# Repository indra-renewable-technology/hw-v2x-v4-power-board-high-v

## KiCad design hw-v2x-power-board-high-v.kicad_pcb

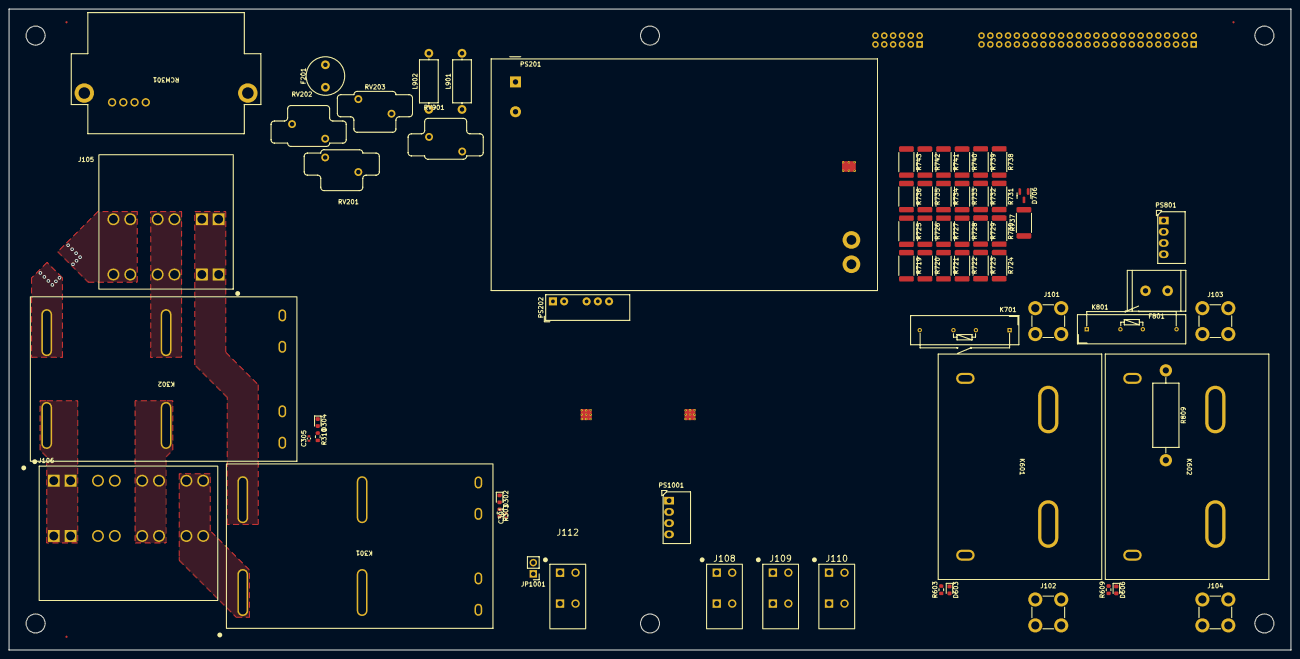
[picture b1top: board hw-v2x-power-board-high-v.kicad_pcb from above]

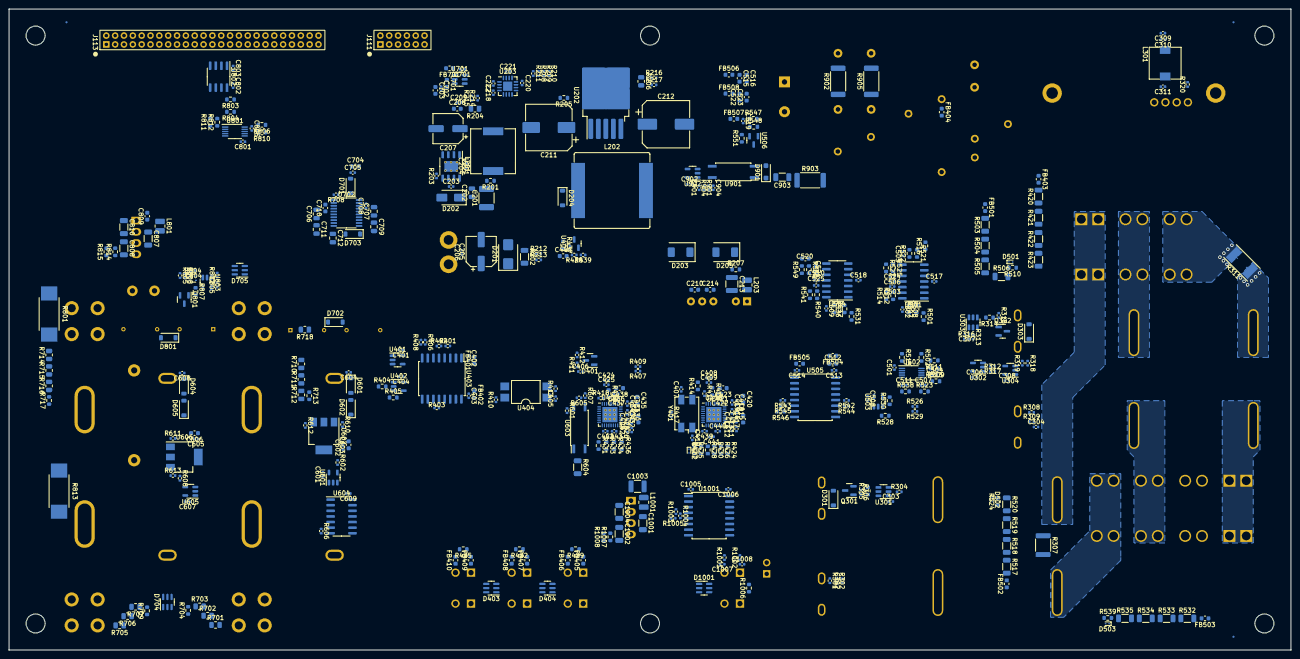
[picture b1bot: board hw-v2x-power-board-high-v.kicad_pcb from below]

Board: 2 copper layers, 290.0 x 145.0 mm, 492 parts (416 on the bottom side), 281 nets.

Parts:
C201: 100uF; C_1812_4532Metric
C202: 10uF; C_0805_2012Metric
C203, C206, C209, C218, C220, C221, C222, C301, C302, C303, C304, C305, C306, C307, C308, C310, C311, C401, C402, C403, C404, C405, C406, C411, C413, C415, C418, C421, C426, C428, C430, C433, C436, C501, C508, C513, C514, C517, C518, C519, C524, C525, C601, C602, C604, C605, C607, C608, C609, C701, C702, C705, C708, C801, C802, C803, C804, C805, C806, C902, C1005, C1006: 0.1uF; C_0402_1005Metric
C204, C408, C424, C440, C441, C442, C443: 10nF; C_0402_1005Metric
C205: 47uF; CP_Elec_6.3x7.7
C207: 100uF; CP_Elec_6.3x7.7
C208, C210, C214, C417, C420, C423, C432, C435, C438, C516, C521, C523, C603, C606: 1uF; C_0603_1608Metric
C211: 100uF; CP_Elec_10x10
C212: 470uF; CP_Elec_10x10.5
C213: 2.2uF; C_1210_3225Metric
C309, C901: 1uF; C_0402_1005Metric
C407, C410: 15pF; C_0402_1005Metric
C409, C412, C414, C416, C419, C422, C425, C427, C429, C431, C434, C437, C504, C507, C511: 150pF; C_0402_1005Metric
C439: 22nF; C_0402_1005Metric
C444, C512, C515, C520, C522: 4.7uF; C_0603_1608Metric
C502, C503, C505, C506, C509, C510: 82nF; C_0402_1005Metric
C703, C704, C809: 10uF; C_0603_1608Metric
C706, C707, C709, C711, C712: 22uF; C_0805_2012Metric
C710: 680nF; C_0603_1608Metric
C807, C810, C1001, C1004: 330pF; C_1206_3216Metric
C808, C1002: 47uF; C_1206_3216Metric
C903: 2n2 1kV; C_1206_3216Metric
C904: 220nF; C_0402_1005Metric
C1003: 10uF; C_1210_3225Metric
C1007, C1008: 47pF; C_0402_1005Metric
D201: P6SMB16A; D_SMB
D202: B320AQ-13-F; D_SMA
D203, D205: SMLVT3V3; SMLVT_SMB
D204: 1N5822; D_SOD-123
D301, D303, D601, D604, D702, D801: B130LAW-7-F; D_SOD-123
D302, D304, D603, D606: Green LED; LED_0603_1608Metric
D401: BAT54C; SOT-23
D402, D501, D502, D503: ESD9B3.3ST5G; D_SOD-923
D403, D404, D704, D705, D1001: CM1293A-04SO; SC-74-6_1.5x2.9mm_P0.95mm
D602, D605: BZT52C36-7-F; D_SOD-123
D701, D703: BAT43W; D_SOD-123
D706: BAV99; SOT-23
D901: SM4007PL-TP; D_SOD-123F
F201: 500mA; 37205000001
F801: TRF600-150-RB; R_Radial_Power_L13.0mm_W9.0mm_P5.00mm
FB401, FB402, FB403, FB404, FB405, FB406, FB407, FB408, FB409, FB410, FB501, FB502, FB503, FB504, FB505, FB506, FB507, FB508, FB701: BLM18AG102SN1D; L_0603_1608Metric
FID101, FID102, FID103, FID104, FID105, FID106: Fiducial; Fiducial_0.5mm_Mask1mm
H101, H102, H103, H104, H105, H106: MountingHole; MountingHole_4.3mm_M4
J101, J102, J103, J104: 74651175R; Wuerth_REDCUBE-THR_WP-THRSH_74651175_THR
J105: NZ 03000B0000G; AMPHENOL_NZ_0300xBxxxxG_3_PIN_CONNECTOR
J106: NZ 04000B0000G; AMPHENOL_NZ_0400xBxxxxG_4_PIN_CONNECTOR
J108, J109, J110, J112: TBLH10-350-02BK; CUI_TBLH10-350-02BK_2_PIN_CONNECTOR
J111: M22-7140642; HARWIN_M22-7140642_12_PIN_CONNECTOR
J113: M22-7142542; HARWIN_M22-7142542_50_PIN_CONNECTOR
JP1001: NO; PinHeader_1x02_P2.54mm_Vertical
K301, K302: AHER2281
K601, K602: OMRON_G9KB-1A; G9KB-1A_DCxx
K701, K801: SHV05-1A85
L201: 15uH; L_Wuerth_WE-TPC_SMT_Shielded
L202: 100uH; L_Bourns_SRP1770TA_16.9x16.9mm
L203, L801, L1001: 22uH; L_1008_2520Metric
L301: 220uH; L_Bourns-SRR7045
L701: 10uH; L_0603_1608Metric
L901, L902: 47uH; L_Axial_L9.5mm_D4.0mm_P12.70mm_Horizontal_Fastron_SMCC
PS201: IRM-60-12; Converter_ACDC_MeanWell_IRM-60-xx_THT
PS202: IA0503S; Converter_DCDC_XP_POWER-IAxxxxS_THT
PS801, PS1001: ROE-1205S
Q301, Q302: DMG2302UK-7; SOT-23
Q801: MMBT5550LT1G; SOT-23
R201, R205, R207, R404, R405, R414, R427, R528, R530, R546, R811, R812: 0R; R_0603_1608Metric
R202: 0.01R; R_1206_3216Metric
R203: 470K; R_0402_1005Metric
R204, R206: 0.033R; R_0805_2012Metric
R208, R209, R210, R211, R301, R302, R306, R308, R309, R315, R320, R406, R407, R408, R409, R415, R418, R526, R529, R708, R1005: 10K; R_0402_1005Metric
R212, R213, R214, R215, R216, R217: 10R; R_0402_1005Metric
R303, R310, R603, R609: 1.8K; R_0603_1608Metric
R304, R312, R313, R317, R318, R319, R602, R608: 4.7K; R_0402_1005Metric
R305, R314, R437, R509, R523, R538: 15R; R_0603_1608Metric
R307: 0R; R_1812_4532Metric
R311: 0.5mR; WSLF2512L5000F
R316, R606, R607, R612, R613, R802, R805: 100K; R_0402_1005Metric
R401, R402, R403, R410, R412: 10k; R_0402_1005Metric
R411, R901: 100R; R_0402_1005Metric
R413, R808: 470R; R_0402_1005Metric
R416, R419, R502, R511, R513, R515: 100R; R_0603_1608Metric
R417: 1M; R_0402_1005Metric
R420, R421, R422, R423, R503, R504, R505, R506, R517, R518, R519, R520, R532, R533, R534, R535: 100K; R_1206_3216Metric
R424, R426, R428, R430, R431, R433, R434, R436, R510: 1K; R_0603_1608Metric
R425: 232R; R_0603_1608Metric
R429, R432, R435: 6.04R; R_0603_1608Metric
R438: 750R; R_0402_1005Metric
R439: 3.16K; R_0402_1005Metric
R501, R507, R508, R512, R514, R516, R521, R522, R525, R527, R531, R536, R537, R540, R541: 10K; R_0603_1608Metric
R524, R539: 2.2K; R_0603_1608Metric
R542, R543, R544, R545, R601, R605: 1K; R_0402_1005Metric
R547: 210R; R_0603_1608Metric
R548: 316R; R_0603_1608Metric
R549, R550, R807: 4.7K; R_0603_1608Metric
R551: 3.16K; R_0603_1608Metric
R604: 620R; R_1206_3216Metric
R610, R611: 47K; R_0402_1005Metric
R701, R702, R703, R705, R706, R707, R710, R711, R712, R714, R715, R716: 240K; R_0805_2012Metric
R704, R709, R713, R717: 3.6K; R_0603_1608Metric
R718: 0R; R_0805_2012Metric
R719, R720, R721, R722, R723, R724, R725, R726, R727, R728, R729, R730, R731, R732, R733, R734, R735, R736, R738, R739, R740, R741, R742, R743: 120K; R_2512_6332Metric
R737: 200R; R_2512_6332Metric
R801, R813: 10R; R_BOURNS_PWR4318
R803, R804: 3K; R_0603_1608Metric
R806, R810: 10R; R_0603_1608Metric
R809: 1R; R_Axial_DIN0614_L14.3mm_D5.7mm_P20.32mm_Horizontal
R814, R815, R1007, R1008: 470R; R_0603_1608Metric
R902, R905: 220R; R_2512_6332Metric
R903: 820K; R_2512_6332Metric
R904: 39K; R_0402_1005Metric
R1001, R1002, R1003, R1004: 0R; R_0402_1005Metric
R1006: 120R; R_0603_1608Metric
RCM301: RCM-EV-02_P
RV201, RV202, RV203, RV901: B72214R2301K101
U201: LM22670; HSOP-8-1EP_3.9x4.9mm_P1.27mm_EP2.41x3.1mm_ThermalVias
U202: LM2576D2TR4-3.3G; TO-263-5_TabPin3
U203: INA3221; Texas_RGV_S-PVQFN-N16_EP2.1x2.1mm
U301, U303: ZXGD3009E6; SOT-23-6
U302, U304: SN74AHC1G08; SOT-23-5
U401: 74AHC1G08; SOT-23-5
U402: 74AHC1G125_X; SOT-23-5
U403, U505: ISO6761DWR; SOIC-16W_7.5x10.3mm_P1.27mm
U404: LTV-817S; SMDIP-4_W9.53mm
U405: STPM33; QFN-32-1EP_5x5mm_P0.5mm_EP3.45x3.45mm_ThermalVias
U406: STPM34; QFN-32-1EP_5x5mm_P0.5mm_EP3.45x3.45mm_ThermalVias
U407, U506: TL431DBZ; SOT-23
U501, U504: MC33174; SOIC-14_3.9x8.7mm_P1.27mm
U502: ADC124S021; VSSOP-10_3x3mm_P0.5mm
U503: 74AHC1G125; SOT-23-5
U601, U605, U803: 74LVC1G08; SOT-23-5
U602, U606: ITS4200SMENHUMA1; SOT-223
U603, U901: HCPL-817-56AE; SO-4_7.6x3.6mm_P2.54mm
U604: 74LV21; SO-14_3.9x8.65mm_P1.27mm
U701: LM2664; SOT-23-6
U702: AD7327; TSSOP-20_4.4x6.5mm_P0.65mm
U801: INA226; VSSOP-10_3x3mm_P0.5mm
U802: Si8602; SOIC-8_3.9x4.9mm_P1.27mm
U804: NL17SZ14; SOT-553
U902: LM321; SOT-23-5
U1001: ISO3082DW; SOIC-16W_7.5x10.3mm_P1.27mm
Y401: 16MHz; Crystal_SMD_EuroQuartz_MQ-4Pin_7.0x5.0mm

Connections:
0V_iso: C210.2, C214.1, C403.1, C405.1, C406.2, C407.2, C408.1, C409.1, C410.2, C411.1, C412.1, C413.1, C414.1, C415.1, C416.1, C417.1, C418.1, C419.1, C420.1, C421.1, C422.1, C423.1, C424.1, C425.1, C426.1, C427.1, C428.1, C429.1, C430.1, C431.1, C432.1, C433.1, C434.1, C435.1, C436.1, C437.1, C438.1, C444.1, D203.2 (A2), D205.1 (A1), D403.2 (VN), D404.2 (VN), FB406.2, FB408.2, FB410.2, PS202.5 (0V), R409.2, R412.1, R427.1, R429.2, R430.2, R432.2, R433.2, R435.2, R436.2, R439.1, U403.9 (GND2), U405.18 (GND_REF), U405.20 (GNDA), U405.22 (GND_REF), U405.26 (GNDD), U405.33 (PAD), U406.3 (XTAL1), U406.18 (GND_REF), U406.20 (GNDA), U406.22 (GND_REF), U406.26 (GNDD), U406.33 (PAD), U407.3 (A), Y401.2, Y401.4
3V3_iso: C210.1, C508.1, D203.1 (A1), D403.5, D404.5, FB402.1, FB504.2, FB506.1, PS202.6 (+Vout), R407.1, R415.1, R418.1, R437.1, R526.1, U503.5
+3.3V: C218.2, C303.1, C306.1, C307.1, C308.1, C401.1, C404.1, C601.2, C607.2, C609.1, C708.1, C803.1, C804.1, C805.1, C902.1, C1005.1, FB401.1, FB505.2, J111.9, J111.11, R206.1, R208.1, R209.1, R210.1, R211.1, R216.1, R301.2, R308.2, R320.2, R401.2, R402.2, R406.1, R410.1, R601.2, R605.2, R708.1, R805.2, R901.1, U203.4 (VS), U203.5 (A0), U203.16 (VPU), U301.1 (VCC), U302.5 (VCC), U303.1 (VCC), U304.5 (VCC), U401.5 (VCC), U402.5, U601.5 (VCC), U604.1, U604.5, U604.14 (VCC), U605.5 (VCC), U702.17 (VDRIVE), U802.1 (AVDD), U803.5 (VCC), U804.5 (VCC), U902.5 (V+), U1001.1 (Vcc1)
+5V: C309.1, C310.1, C704.1, C705.1, D701.2 (A), D702.1 (K), D704.5, D705.5, D706.2 (A), D801.1 (K), J111.5, J111.7, K701.2, K801.2, L301.1, R204.1, R207.2, R214.1, U701.4 (~SD), U701.5 (V+), U702.16 (VCC)
+5V_ISO1: C1001.2, C1002.2, C1006.1, D1001.5, PS1001.4 (+Vout), R1007.1, R1008.1, U1001.16 (Vcc2)
+12V: C301.1, C602.1, C603.1, C605.1, C606.1, C809.2, C1003.2, D301.1 (K), J111.1, J111.3, K301.3, K301.5, L801.1, L1001.1, R201.1, R202.1, R205.2, R212.1, R303.2, U602.4 (IN), U606.4 (IN)
-3V3_iso: C214.2, D205.2 (A2), FB508.1, PS202.4 (-Vout)
/1P_SHUNT_L1_N: R311.2, R426.2
/1P_SHUNT_L1_P: R311.3, R424.2
/A7NS_I2C1_SCL: J113.24, U203.6 (SCL), U802.3 (ASCL)
/A7NS_I2C1_SDA: J113.28, U203.7 (SDA), U802.2 (ASDA)
/A7NS_SPI1_CLK: J113.35, U403.2 (INA), U702.20 (SCLK)
/A7NS_SPI1_MISO: J113.39, R405.2, U402.4, U702.18 (DOUT)
/A7NS_SPI1_MOSI: J113.43, U403.3 (INB), U702.2 (DIN)
/AC-metering/clk_stpm: R414.1, U405.1 (CLKOUT), U406.2 (XTAL2)
/AC-metering/cs1: R415.2, U403.13 (OUTC), U405.29 (SCS)
/AC-metering/cs2: R418.2, U403.12 (OUTD), U406.29 (SCS)
/AC-metering/en: C406.1, R411.1, U405.8 (EN), U406.8 (EN)
/AC-metering/iin_L1: C440.1, R426.1, U405.13 (IIN2)
/AC-metering/iin_ext_aux_1: C442.1, R433.1, U406.12 (IIN1)
/AC-metering/iin_ext_aux_2: C443.1, R436.1, U406.14 (IIP2)
/AC-metering/iin_ext_house: C441.1, R430.1, U405.12 (IIN1)
/AC-metering/iip_L1: C440.2, R424.1, U405.14 (IIP2)
/AC-metering/iip_ext_aux_1: C442.2, R431.1, U406.11 (IIP1)
/AC-metering/iip_ext_aux_2: C443.2, R434.1, U406.13 (IIN2)
/AC-metering/iip_ext_house: C441.2, R428.1, U405.11 (IIP1)
/AC-metering/metering_ext_aux_ct_1_neg: D404.6, FB408.1, J109.2
/AC-metering/metering_ext_aux_ct_1_pos: D404.4, FB407.1, J109.1
/AC-metering/metering_ext_aux_ct_2_neg: D403.6, FB410.1, J110.2
/AC-metering/metering_ext_aux_ct_2_pos: D403.4, FB409.1, J110.1
/AC-metering/metering_ext_house_ct_neg: D404.3 (CH1), FB406.1, J108.2
/AC-metering/metering_ext_house_ct_pos: D404.1 (CH1), FB405.1, J108.1
/AC-metering/mi: R404.1, R405.1, R406.2, R408.1, U403.7 (OUTF)
/AC-metering/miso: R407.2, R409.1, U403.10 (INF), U405.32 (MISO), U406.32 (MISO)
/AC-metering/mosi: U403.14 (OUTB), U405.31 (MOSI), U406.31 (MOSI)
/AC-metering/sclk: D401.1, U403.15 (OUTA), U405.30 (SCL), U406.30 (SCL)
/AC-metering/syn: C408.2, C409.2, C424.2, C425.2, D401.2, R403.1, R416.1, R419.1, U403.11 (OUTE)
/AC-metering/v_stpm: C405.2, C418.2, C419.2, C420.2, C433.2, C434.2, C435.2, C444.2, R403.2, R437.2, R438.2, U404.1, U405.23 (VCC), U406.23 (VCC), U407.1 (K)
/AC-metering/vip_L1: C439.2, D402.1 (A1), R423.1, R425.1, U405.9 (VIP1), U406.9 (VIP1), U406.16 (VIP2)
/AC-metering/vip_N1: C439.1, D402.2 (A2), FB404.2, R425.2, R427.2, U405.10 (VIN1), U406.10 (VIN1), U406.15 (VIN2)
/AC-metering/zcr: R413.1, R414.2, U406.1 (CLKOUT)
/AC-switching/12v_switched: C305.1, D303.1 (K), K301.10, K302.5, R310.2
/AC-switching/ac_cpc_out: J105.1, K301.12, R307.1
/AC-switching/ac_l1_out: J105.2, K302.10
/AC-switching/ac_neutral_out: J105.3, R311.4
/AC-switching/neut_sw: K302.12, R311.1
/AC_EARTH_RELAY_EN: J113.32, R304.2
/AC_EARTH_RELAY_SENSE: C302.1, J113.40, R302.2
/AC_POWER_RELAY_EN: J113.34, R312.2
/AC_POWER_RELAY_SENSE: C304.1, J113.38, R309.2
/AC_RCM_TEST: J113.44, RCM301.3 (TEST)
/CPC_IN: FB502.1, J106.4, K301.1, R307.2, RV202.2, RV203.2
/DC-switching-and-measurement/HVDC-insulation-leakage-detection/+5V_ISO: C801.1, C802.2, C807.2, C808.2, PS801.4 (+Vout), R803.1, R804.1, R814.1, R815.1, U801.6 (VS), U802.8 (BVDD)
/DC-switching-and-measurement/HVDC-insulation-leakage-detection/GND_ISO: C801.2, C802.1, C808.1, C810.2, PS801.3 (-Vout), R809.2, R810.1, R811.2, R812.2, R813.1, R814.2, R815.2, U801.7 (GND), U802.5 (BGND)
/DC-switching-and-measurement/HVDC-insulation-leakage-detection/shunt_high: K801.1, R806.1, R809.1, U801.8 (Vbus)
/DC-switching-and-measurement/HVDC-voltage-measurement/-5V: C702.1, C703.1, D703.1 (K), D706.1 (K), L701.2
/DC-switching-and-measurement/HVDC-voltage-measurement/AGND: C704.2, C705.2, C706.2, C707.2, C709.2, C710.2, C711.2, C712.2, D704.2 (VN), D705.2 (VN), FB701.2, R704.1, R709.1, R713.1, R717.1, R737.1, U702.4 (AGND), U702.7 (VIN0), U702.11 (VIN7), U702.12 (VIN6)
/DC-switching-and-measurement/HVDC-voltage-measurement/dc_sense_battery_pos_swi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: K701.4, R710.2, R718.1, R719.2, R720.2, R721.2, R722.2, R723.2, R724.2
/DC-switching-and-measurement/dc_input_battery_neg: J103.1, K602.3, R714.2, R738.1, R739.1, R740.1, R741.1, R742.1, R743.1, R801.2
/DC-switching-and-measurement/dc_input_battery_pos: J101.1, K601.3, K701.1, R718.2
/DC-switching-and-measurement/dc_neg_contactor_drive: C608.1, D604.1 (K), K602.1, R609.2, R611.1, U606.1 (OUT)
/DC-switching-and-measurement/dc_neg_en: R608.2, R805.1, R808.1, U605.4
/DC-switching-and-measurement/dc_output_inverter_neg: J104.1, K602.4, R705.2, R813.2
/DC-switching-and-measurement/dc_output_inverter_pos: J102.1, K601.4, R701.2
/DC-switching-and-measurement/dc_pos_contactor_drive: C604.1, D601.1 (K), K601.1, R603.2, R610.1, U602.1 (OUT)
/DC-switching-and-measurement/dc_pos_en: R602.2, U601.4
/DC_CONTACTOR_NEG: J113.13, U605.1
/DC_CONTACTOR_POS: J113.11, U601.1
/DC_I_SHUNT_EN: J113.19, R802.1, U803.1
/DC_VOLTAGE_CS: J113.5, R708.2, U702.1 (~CS)
/ESTOP_LATCH: J113.17, R318.2, U604.2
/HVIL_MON: J113.7, R605.1, R607.2, U603.3, U604.4
/L1_IN: F201.1, FB403.1, FB501.1, J106.3, K302.3, RV201.1, RV202.1
/M4_SPI2_CLK: J113.14, U505.2 (INA)
/M4_SPI2_MISO: J113.6, R546.2
/M4_SPI2_MOSI: J113.10, U505.3 (INB)
/METERING_CS1: J113.16, R401.1, U401.1, U403.4 (INC)
/METERING_CS2: J113.18, R402.1, U401.2, U403.5 (IND)
/METERING_SYN: J113.27, U403.6 (INE)
/METERING_ZCR: J113.23, R410.2, U404.4
/NEUTRAL_IN: C501.2, C503.2, C504.2, C506.2, C507.2, C508.2, C510.2, C511.2, C512.1, C513.2, C515.2, C516.2, C517.2, C518.2, C519.2, C520.2, C521.2, C522.1, C523.1, C524.1, C525.1, D501.2 (A2), D502.2 (A2), D503.2 (A2), FB404.1, J106.1, K302.1, PS201.2 (AC/N), R510.1, R514.1, R524.1, R527.1, R529.2, R539.1, R541.1, R542.1, R544.1, R550.1, R551.1, RV201.2, RV203.1, U502.3 (GND), U503.3, U504.5 (+), U505.9 (GND2), U506.3 (A)
/PESTS_CS: J113.20, U505.4 (INC)
/PESTSs/buf_miso: R530.2, U503.4, U505.10 (INF)
/PESTSs/cpc_neutral_meas: C507.1, R523.1, U502.6 (IN2)
/PESTSs/l1_neutral_meas: C504.1, R509.1, U502.7 (IN1)
/PESTSs/miso: R511.1, R526.2, R528.1, R529.1, R530.1
/PESTSs/mosi: R513.1, U505.14 (OUTB)
/PESTSs/sclk: R502.1, U505.15 (OUTA)
/PESTSs/tt_ref_neutral_meas: C511.1, R538.1, U502.5 (IN3)
/PESTSs/v_mid_ref: R501.2, R516.2, R531.2, U502.4 (IN4), U504.8, U504.9 (-)
/PESTSs/v_ref: C501.1, C520.1, R547.2, R548.2, R549.2, U502.2 (VA), U506.1 (K)
/PESTSs/~cs: R515.1, U503.1, U505.13 (OUTC)
/RCM_DC_ERROR: J113.46, R319.2, R320.1, RCM301.4 (FAULT)
/RS485/RS485_N: C1007.1, D1001.6, J112.2, JP1001.2 (B), R1001.1
/RS485/RS485_P: C1008.1, D1001.4, J112.1, R1002.1, R1006.1
/RS485/UART_RE: R1004.1, U1001.4 (~RE)
/TT_REF: FB503.1, J106.2
/ZC_DIGITAL: J113.31, U902.3 (-), U902.4
/main-power-supplies/3V3_SNS+: C222.1, R217.2, U203.2 (IN+3)
/main-power-supplies/3V3_SNS-: C222.2, R216.2, U203.1 (IN-3)
/main-power-supplies/5V_SNS+: C221.1, R215.2, U203.15 (IN+2)
/main-power-supplies/5V_SNS-: C221.2, R214.2, U203.14 (IN-2)
/main-power-supplies/12V_SNS+: C220.1, R213.2, U203.12 (IN+1)
/main-power-supplies/12V_SNS-: C220.2, R212.2, U203.11 (IN-1)
/main-power-supplies/LIVE_TO_ZC: F201.2, L902.2, PS201.1 (AC/L), R905.2
/main-power-supplies/NEUTRAL_IN: L901.2, R902.2
GND: C201.1, C202.1, C203.1, C205.2, C206.2, C207.2, C208.1, C209.1, C211.2, C212.2, C213.2, C218.1, C301.2, C302.2, C303.2, C304.2, C305.2, C306.2, C307.2, C308.2, C309.2, C310.2, C311.2, C401.2, C402.2, C404.2, C514.1, C601.1, C602.2, C603.2, C604.2, C605.2, C606.2, C607.1, C608.2, C609.2, C702.2, C703.2, C708.2, C803.2, C804.2, C805.2, C809.1, C810.1, C901.2, C902.2, C904.2, C1003.1, C1004.1, C1005.2, D201.2 (A2), D202.2 (A), D204.2 (A), D602.1 (K), D603.1 (K), D605.1 (K), D606.1 (K), D702.2 (A), FB701.1, J111.2, J111.4, J111.6, J111.8, J111.10, J111.12, J113.1, J113.2, J113.3, J113.4, J113.8, J113.9, J113.12, J113.15, J113.21, J113.22, J113.25, J113.26, J113.29, J113.30, J113.33, J113.36, J113.37, J113.41, J113.42, J113.45, J113.47, J113.48, J113.49, J113.50, K301.7, K302.7, K601.2, K602.2, K701.3, PS201.4 (-Vout), PS202.2 (-Vin), PS801.1 (-Vin), PS1001.1 (-Vin), Q301.2 (S), Q302.2 (S), Q801.2 (E), R306.1, R315.1, R316.1, R408.2, R543.2, R545.2, R606.2, R607.1, R610.2, R611.2, R612.2, R613.2, R802.2, R1005.2, RCM301.1 (0V), U201.6 (GND), U201.9 (GND), U202.3 (GND), U202.5 (~ON/OFF), U203.3 (GND), U301.3 (VEE), U302.3 (GND), U303.3 (VEE), U304.3 (GND), U401.3 (GND), U402.3, U403.8 (GND1), U404.3, U505.8 (GND1), U601.3 (GND), U602.2 (GND), U603.2, U604.7 (GND), U604.9, U604.10, U604.12, U604.13, U605.3 (GND), U606.2 (GND), U701.1 (GND), U702.3 (DGND), U702.19 (DGND), U802.4 (AGND), U803.3 (GND), U804.3 (VSS), U901.3, U902.2 (V-), U1001.2 (GND1), U1001.7 (GND1), U1001.8 (GND1)
GND_ISO1: C1002.1, C1004.2, C1007.2, C1008.2, D1001.2 (VN), PS1001.3 (-Vout), R1007.2, R1008.2, U1001.9 (GND2), U1001.10 (GND2), U1001.15 (GND2)
unnamed: C213.1, L203.1, R207.1
unnamed: C502.1, R509.2, R512.1, U501.14
unnamed: C502.2, R501.1, R507.1, R508.2
unnamed: C505.1, R523.2, R525.1, U501.8
unnamed: C505.2, R516.1, R521.1, R522.2
unnamed: C509.1, R538.2, R540.1, U504.14
unnamed: C509.2, R531.1, R536.1, R537.2
unnamed: C519.1, FB507.2, R547.1
unnamed: C901.1, R901.2, R904.1
unnamed: C903.1, R903.1
unnamed: C205.1, C206.1, D201.1 (A1), PS201.3 (+Vout), R202.2, R213.1
unnamed: C204.1, D202.1 (K), L201.1, U201.8 (SW)
unnamed: D204.1 (K), L202.1, U202.2 (OUT)
unnamed: D301.2 (A), D302.1 (K), K301.8, Q301.3 (D)
unnamed: D302.2 (A), R303.1
unnamed: D303.2 (A), D304.1 (K), K302.8, Q302.3 (D)
unnamed: D304.2 (A), R310.1
unnamed: D401.3, R411.2, R412.2
unnamed: D501.1 (A1), R506.1, R510.2, U501.3 (+)
unnamed: D502.1 (A1), R520.1, R524.2, U501.5 (+)
unnamed: D503.1 (A1), R535.1, R539.2, U504.3 (+)
unnamed: D601.2 (A), D602.2 (A)
unnamed: D603.2 (A), R603.1
unnamed: D604.2 (A), D605.2 (A)
unnamed: D606.2 (A), R609.1
unnamed: D701.1 (K), U702.15 (VDD)
unnamed: D703.2 (A), U702.6 (VSS)
unnamed: D801.2 (A), K801.3, Q801.3 (C)
unnamed: D901.2 (A), L902.1, R905.1, RV901.2, U901.2
unnamed: C903.2, D901.1 (K), U901.1
unnamed: F801.1, R801.1
unnamed: F801.2, K801.4
unnamed: FB403.2, R420.2
unnamed: FB405.2, R428.2, R429.1
unnamed: FB407.2, R431.2, R432.1
unnamed: FB409.2, R434.2, R435.1
unnamed: FB501.2, R503.2
unnamed: FB502.2, R517.2
unnamed: FB503.2, R532.2
unnamed: JP1001.1 (A), R1006.2
unnamed: K301.6, R301.1, R302.1
unnamed: K302.6, R308.1, R309.1
unnamed: L901.1, R902.1, R903.2, RV901.1
unnamed: L203.2, PS202.1 (+Vin)
unnamed: C807.1, L801.2, PS801.2 (+Vin)
unnamed: C1001.1, L1001.2, PS1001.2 (+Vin)
unnamed: Q301.1 (G), R305.1, R306.2
unnamed: Q302.1 (G), R314.1, R315.2
unnamed: Q801.1 (B), R807.2
unnamed: R312.1, U302.1
unnamed: R313.2, R316.2, U302.4
unnamed: R317.1, U304.4
unnamed: R317.2, U302.2
unnamed: R318.1, U304.1
unnamed: R319.1, U304.2
unnamed: R404.2, U402.2
unnamed: R413.2, U404.2
unnamed: R420.1, R421.2
unnamed: R421.1, R422.2
unnamed: R422.1, R423.2
unnamed: R503.1, R504.2
unnamed: R504.1, R505.2
unnamed: R505.1, R506.2
unnamed: R517.1, R518.2
unnamed: R518.1, R519.2
unnamed: R519.1, R520.2
unnamed: R528.2, U503.2
unnamed: R532.1, R533.2
unnamed: R533.1, R534.2
unnamed: R534.1, R535.2
unnamed: R601.1, U603.4
unnamed: R604.1, U603.1
unnamed: R606.1, U601.2, U604.6, U605.2
unnamed: R701.1, R702.2
unnamed: R702.1, R703.2
unnamed: R705.1, R706.2
unnamed: R706.1, R707.2
unnamed: R710.1, R711.2
unnamed: R711.1, R712.2
unnamed: R714.1, R715.2
unnamed: R715.1, R716.2
unnamed: R719.1, R725.2
unnamed: R720.1, R726.2
unnamed: R721.1, R727.2
unnamed: R722.1, R728.2
unnamed: R723.1, R729.2
unnamed: R724.1, R730.2
unnamed: R731.1, R738.2
unnamed: R732.1, R739.2
unnamed: R733.1, R740.2
unnamed: R734.1, R741.2
unnamed: R735.1, R742.2
unnamed: R736.1, R743.2
unnamed: R807.1, U803.4
unnamed: R808.2, U804.2
unnamed: C311.1, L301.2, RCM301.2 (+V)
unnamed: C204.2, U201.1 (BOOT)
unnamed: R203.1, U201.5 (EN)
unnamed: C207.1, C208.2, C209.2, L201.2, R204.2, R215.1, U201.4 (FB)
unnamed: C201.2, C202.2, C203.2, R201.2, R203.2, U201.7 (VIN)
unnamed: C212.1, L202.2, R206.2, R217.1, U202.4 (FB)
unnamed: C211.1, R205.1, U202.1 (VIN)
unnamed: R209.2, U203.9 (CRITICAL)
unnamed: R208.2, U203.10 (PV)
unnamed: R211.2, U203.13 (TC)
unnamed: R210.2, U203.8 (WARNING)
unnamed: R304.1, U301.2 (IN)
unnamed: R305.2, U301.4 (SINK), U301.6 (SOURCE)
unnamed: R313.1, U303.2 (IN)
unnamed: R314.2, U303.4 (SINK), U303.6 (SOURCE)
unnamed: U401.4, U402.1
unnamed: C402.1, FB401.2, U403.1 (Vcc1)
unnamed: C403.2, FB402.2, U403.16 (Vcc2)
unnamed: R416.2, U405.28 (SYN)
unnamed: C415.2, C416.2, C417.2, U405.21 (VDDA)
unnamed: C421.2, C422.2, C423.2, U405.27 (VDDD)
unnamed: C411.2, C412.2, U405.17 (VREF1)
unnamed: C413.2, C414.2, U405.19 (VREF2)
unnamed: C410.1, R417.2, U405.3 (XTAL1), Y401.1
unnamed: C407.1, R417.1, U405.2 (XTAL2), Y401.3
unnamed: R419.2, U406.28 (SYN)
unnamed: C430.2, C431.2, C432.2, U406.21 (VDDA)
unnamed: C436.2, C437.2, C438.2, U406.27 (VDDD)
unnamed: C426.2, C427.2, U406.17 (VREF1)
unnamed: C428.2, C429.2, U406.19 (VREF2)
unnamed: R438.1, R439.2, U407.2 (REF)
unnamed: R507.2, U501.1, U501.2 (-)
unnamed: R521.2, U501.6 (-), U501.7
unnamed: C506.1, R522.1, U501.10 (+)
unnamed: R525.2, R527.2, U501.9 (-)
unnamed: C503.1, R508.1, U501.12 (+)
unnamed: R512.2, R514.2, U501.13 (-)
unnamed: C515.1, C516.1, C517.1, C518.1, FB506.2, FB507.1, U501.4 (V+), U504.4 (V+)
unnamed: C522.2, C523.2, C524.2, C525.2, FB508.2, U501.11 (V-), U504.11 (V-)
unnamed: R502.2, U502.10 (CLK)
unnamed: R513.2, U502.8 (Din)
unnamed: R511.2, U502.9 (Dout)
unnamed: R515.2, U502.1 (~CS)
unnamed: R536.2, U504.1, U504.2 (-)
unnamed: U504.6 (-), U504.7
unnamed: C521.1, R549.1, R550.2, U504.10 (+)
unnamed: C510.1, R537.1, U504.12 (+)
unnamed: R540.2, R541.2, U504.13 (-)
unnamed: R543.1, U505.5 (IND)
unnamed: R545.1, U505.6 (INE)
unnamed: R542.2, U505.12 (OUTD)
unnamed: R544.2, U505.11 (OUTE)
unnamed: R546.1, U505.7 (OUTF)
unnamed: C514.2, FB505.1, U505.1 (Vcc1)
unnamed: C512.2, C513.1, FB504.1, U505.16 (Vcc2)
unnamed: R548.1, R551.2, U506.2 (REF)
unnamed: R602.1, R612.1, U602.3 (ON/~OFF)
unnamed: R608.1, R613.1, U606.3 (ON/~OFF)
unnamed: C701.1, U701.6 (CAP+)
unnamed: C701.2, U701.3 (CAP-)
unnamed: L701.1, U701.2 (OUT)
unnamed: C710.1, U702.5 (REF)
unnamed: C706.1, D704.3 (CH1), R703.1, R704.2, U702.8 (VIN1)
unnamed: C707.1, D704.1 (CH1), R707.1, R709.2, U702.14 (VIN2)
unnamed: C709.1, D705.1 (CH1), R712.1, R713.2, U702.13 (VIN3)
unnamed: C711.1, D705.4, R716.1, R717.2, U702.9 (VIN4)
unnamed: C712.1, D706.3 (K), R725.1, R726.1, R727.1, R728.1, R729.1, R730.1, R731.2, R732.2, R733.2, R734.2, R735.2, R736.2, R737.2, U702.10 (VIN5)
unnamed: R811.1, U801.2 (A0)
unnamed: R812.1, U801.1 (A1)
unnamed: R804.2, U801.5 (SCL), U802.6 (BSCL)
unnamed: R803.2, U801.4 (SDA), U802.7 (BSDA)
unnamed: C806.1, R806.2, U801.10 (Vin+)
unnamed: C806.2, R810.2, U801.9 (Vin-)
unnamed: U803.2, U804.4
unnamed: C904.1, R904.2, U901.4, U902.1 (+)
unnamed: R1002.2, U1001.12 (A)
unnamed: R1001.2, U1001.13 (B)
unnamed: R1003.1, R1004.2, R1005.1, U1001.5 (DE)
